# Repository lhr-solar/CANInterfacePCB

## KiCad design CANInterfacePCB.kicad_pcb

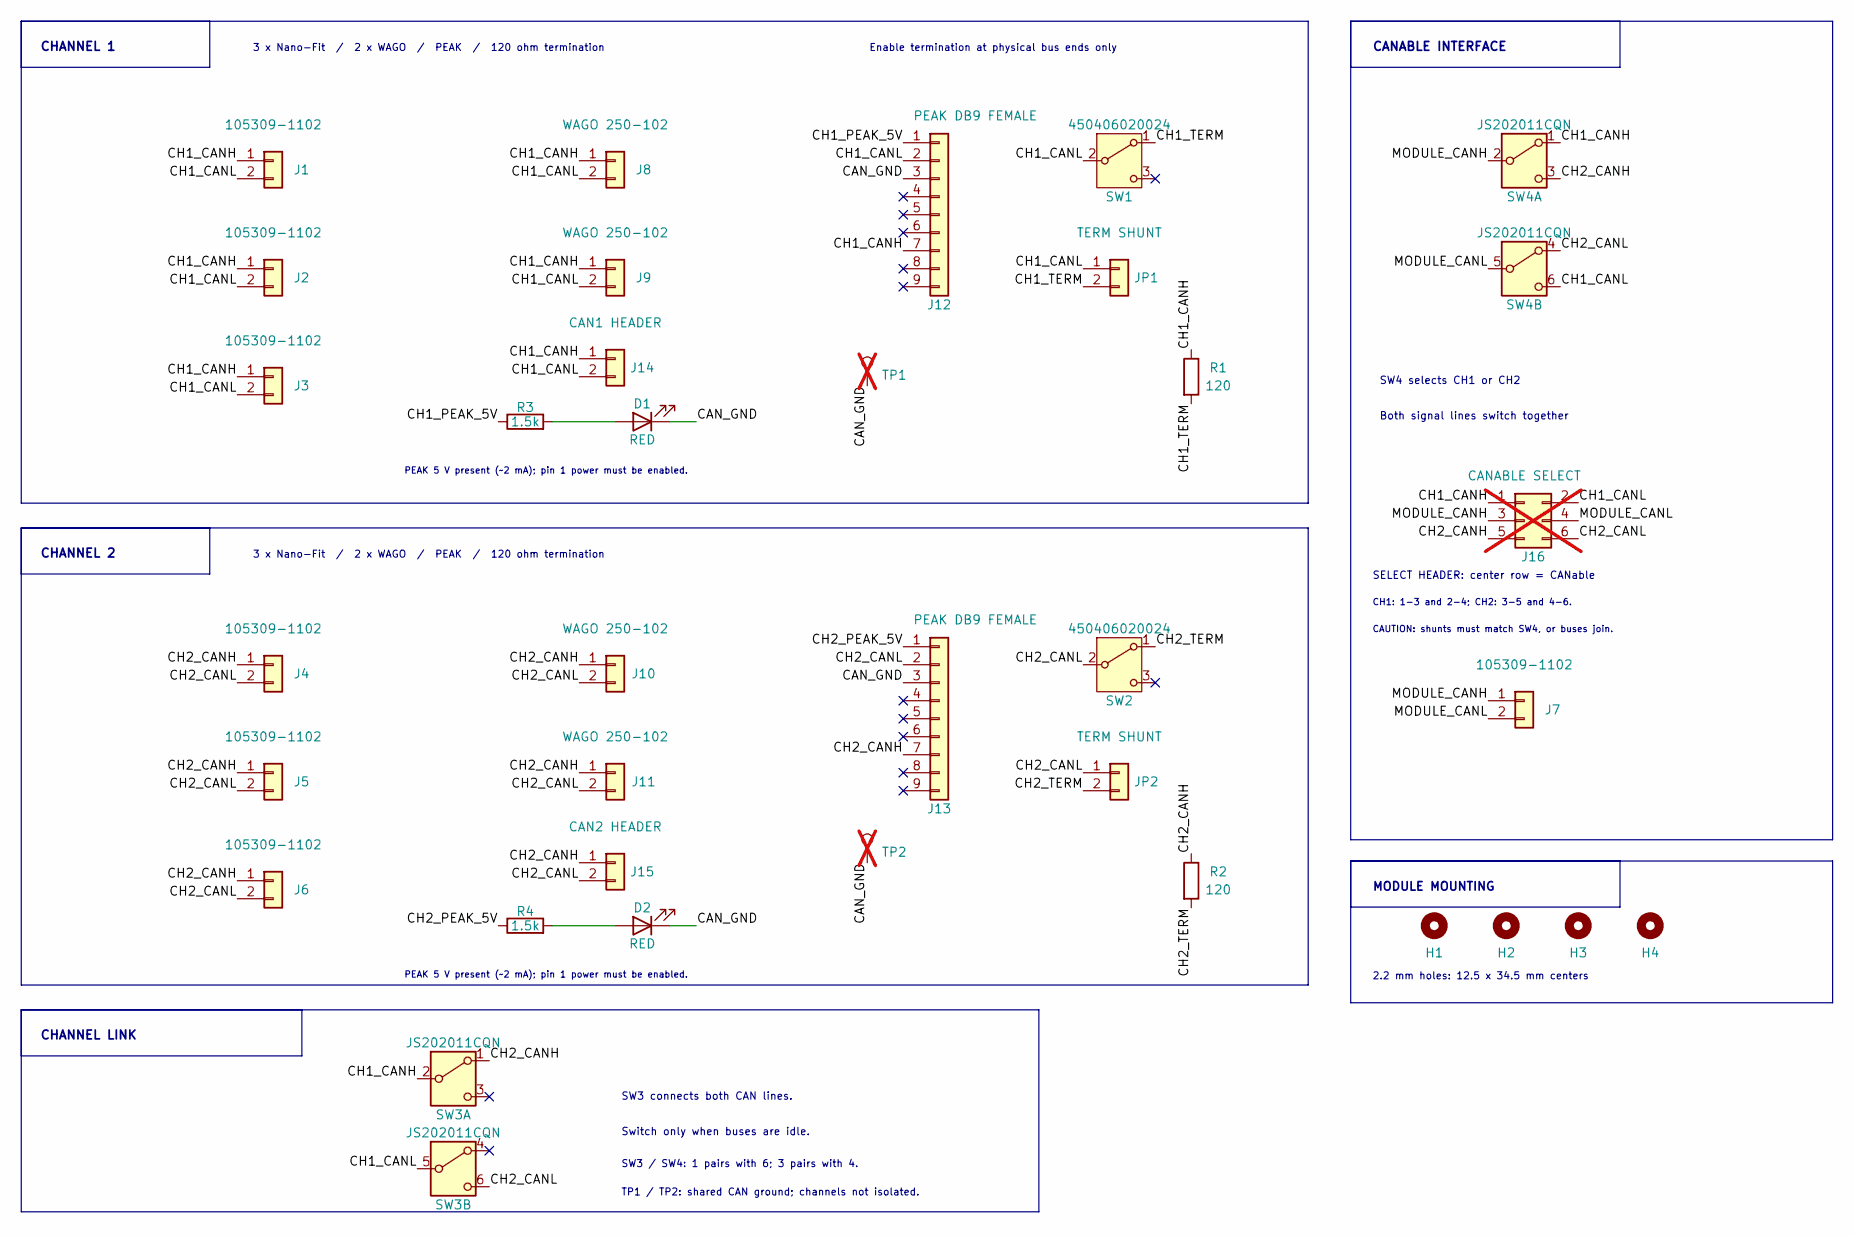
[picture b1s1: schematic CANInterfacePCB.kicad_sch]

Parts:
D1, D2: RED; LED_0603_1608Metric; MPN LTST-C193KRKT-2A
H1, H2, H3, H4: CANable M2; MountingHole_2.2mm_M2
J1, J2, J3, J4, J5, J6, J7: 105309-1102; Molex_Nano-Fit_105309-xx02_1x02_P2.50mm_Vertical; MPN 105309-1102
J8, J9, J10, J11: WAGO 250-102; WAGO_250-102; MPN 250-102
J12, J13: PEAK DB9 FEMALE; AMPHENOL_L77SDE09SA4CH3R; MPN L77SDE09SA4CH3R
J14: CAN1 HEADER; PinHeader_1x02_P2.54mm_Vertical; MPN TSW-102-07-G-S
J15: CAN2 HEADER; PinHeader_1x02_P2.54mm_Vertical; MPN TSW-102-07-G-S
J16: CANABLE SELECT; PinHeader_2x03_P2.54mm_Vertical; MPN TSW-103-07-G-D; not fitted
JP1, JP2: TERM SHUNT; PinHeader_1x02_P2.54mm_Vertical; MPN TSW-102-07-G-S
R1, R2: 120; R_0603_1608Metric; Tolerance 1%; MPN RC0603FR-07120RL
R3, R4: 1.5k; R_0603_1608Metric; Tolerance 1%; MPN RC0603FR-071K5L
SW1, SW2: 450406020024; BootSW; MPN 450406020024
SW3, SW4: JS202011CQN; SW_CK_JS202011CQN_ClockwisePinNumbering
TP1: CH1 CAN_GND; TestPoint_Pad_D2.0mm; not fitted
TP2: CH2 CAN_GND; TestPoint_Pad_D2.0mm; not fitted

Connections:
/CAN_GND: D1.1 (K), D2.1 (K), J12.3, J13.3, TP1.1, TP2.1
/CH1_CANH: J1.1, J2.1, J3.1, J8.1, J9.1, J12.7, J14.1, J16.1, R1.1, SW3.2 (B), SW4.1 (A)
/CH1_CANL: J1.2, J2.2, J3.2, J8.2, J9.2, J12.2, J14.2, J16.2, JP1.1, SW1.2 (B), SW3.5 (B), SW4.6 (C)
/CH1_PEAK_5V: J12.1, R3.1
/CH1_TERM: JP1.2, R1.2, SW1.1 (A)
/CH2_CANH: J4.1, J5.1, J6.1, J10.1, J11.1, J13.7, J15.1, J16.5, R2.1, SW3.1 (A), SW4.3 (C)
/CH2_CANL: J4.2, J5.2, J6.2, J10.2, J11.2, J13.2, J15.2, J16.6, JP2.1, SW2.2 (B), SW3.6 (C), SW4.4 (A)
/CH2_PEAK_5V: J13.1, R4.1
/CH2_TERM: JP2.2, R2.2, SW2.1 (A)
/MODULE_CANH: J7.1, J16.3, SW4.2 (B)
/MODULE_CANL: J7.2, J16.4, SW4.5 (B)
unnamed: D1.2 (A), R3.2
unnamed: D2.2 (A), R4.2

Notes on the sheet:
SELECT HEADER: center row = CANable
3 x Nano-Fit / 2 x WAGO / PEAK / 120 ohm termination
Enable termination at physical bus ends only
MODULE MOUNTING
Switch only when buses are idle.
SW3 connects both CAN lines.
SW4 selects CH1 or CH2
SW3 / SW4: 1 pairs with 6; 3 pairs with 4.
CAUTION: shunts must match SW4, or buses join.
CHANNEL 2
PEAK 5 V present (~2 mA); pin 1 power must be enabled.
CHANNEL LINK
TP1 / TP2: shared CAN ground; channels not isolated.
CH1: 1-3 and 2-4; CH2: 3-5 and 4-6.
2.2 mm holes: 12.5 x 34.5 mm centers
CANABLE INTERFACE
CHANNEL 1
Both signal lines switch together

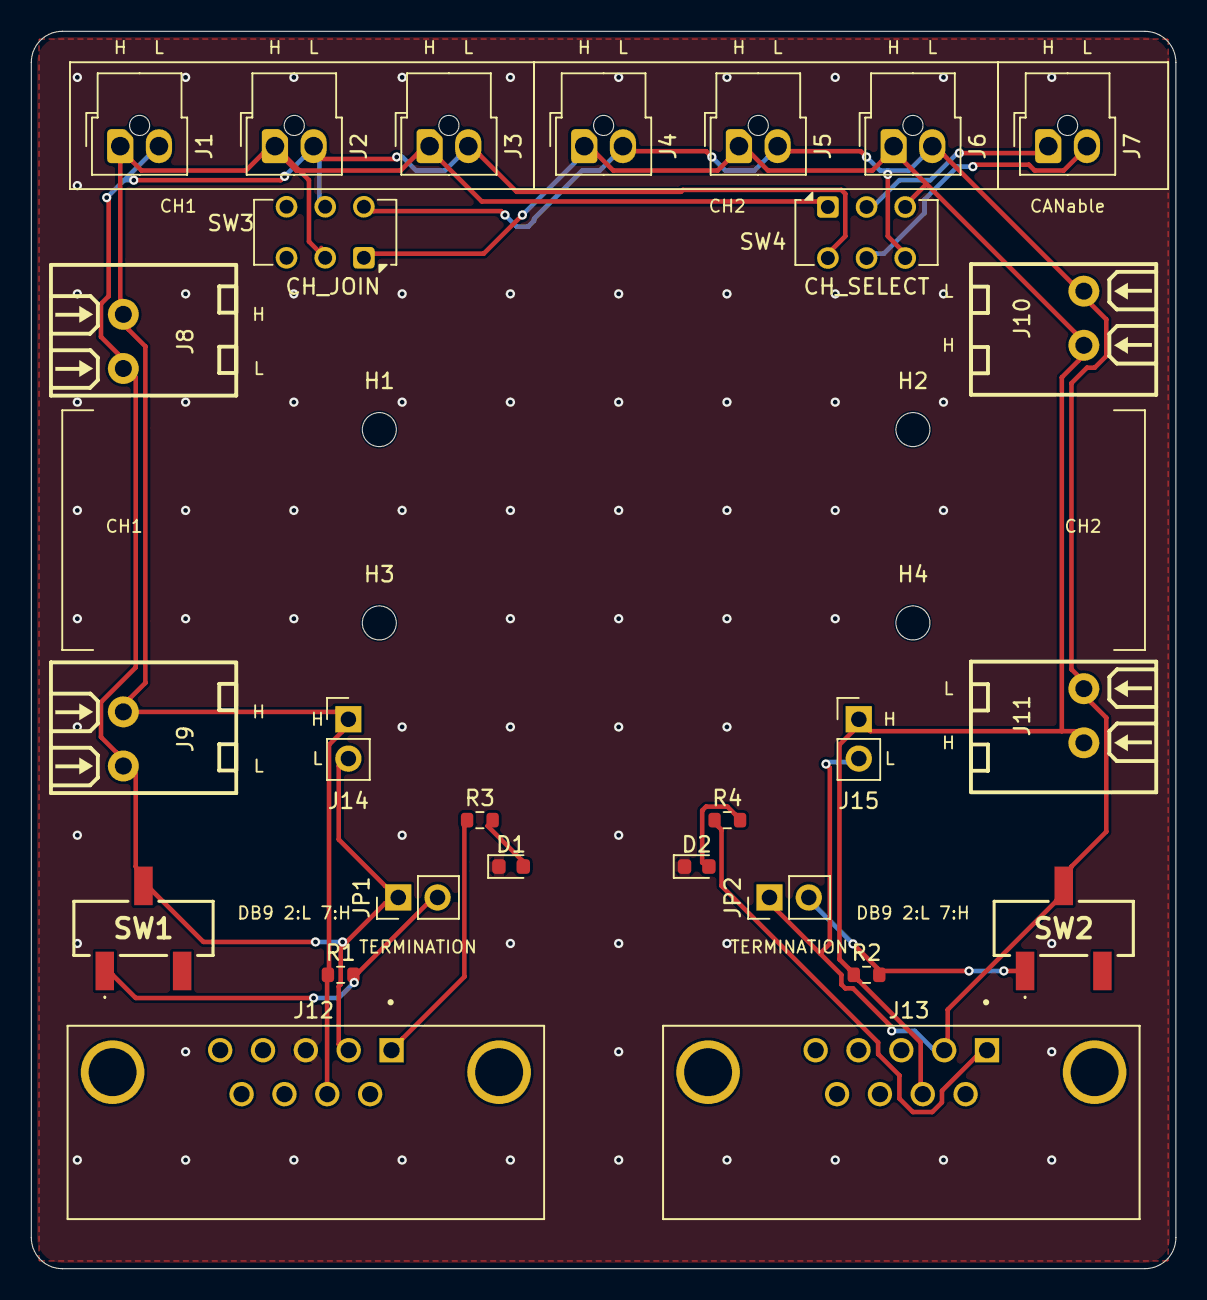
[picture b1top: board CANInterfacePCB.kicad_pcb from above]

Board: 2 copper layers, 74.0 x 80.0 mm, 31 parts (0 on the bottom side), 13 nets.

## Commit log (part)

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2025-10-18 gitignore
2025-10-18 init
2025-10-18 layout sum1 trace
2025-10-18 Parthiv sucks
2025-10-18 silkscreen
2025-10-18 done
2025-10-18 gerbers
2025-10-18 stuff
